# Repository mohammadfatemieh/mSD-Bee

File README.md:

# mSD-Bee
XBee footprint compatible Module with microSD Socket.

* microSD-Socket
* SPI interface
* XBee compatible Pinout (3.3V)
* Open-Source and released under the [Creative Commons Attribution Share-Alike License](https://creativecommons.org/licenses/by-sa/4.0/).
* **[Documentation on learn.watterott.com](https://learn.watterott.com)**

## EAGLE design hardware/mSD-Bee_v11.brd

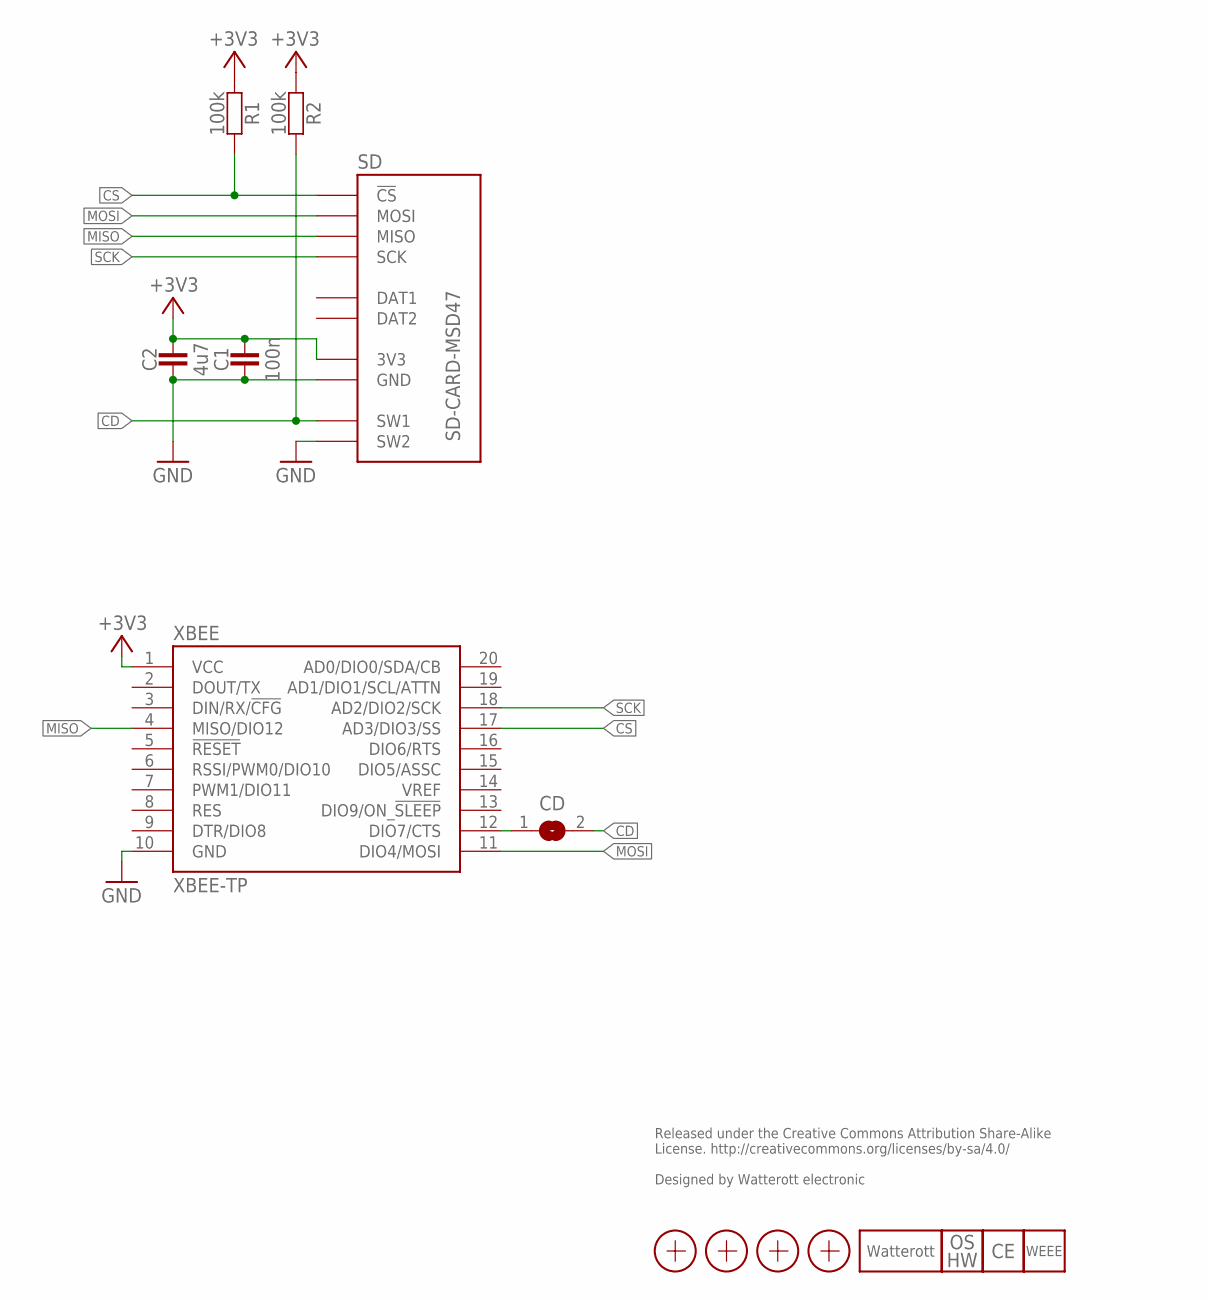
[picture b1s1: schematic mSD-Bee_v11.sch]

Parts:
C1: 100n; C0402
C2: 4u7; C0603
CD: JUMPER2-0603
LOGO3: LOGO_SPARK-2; SPARK_2MM
LOGO4: LOGO_OSHW-2; OSHW_2MM
LOGO5: LOGO_CE-2; CE_2MM
LOGO6: LOGO_WEEE-4; WEEE_4MM
R1, R2: 100k; C0402
SD: SD-CARD-MSD47; SD_47309XXXX
X1, X2, X3, X4: PASSER-07; PASSER_07MM
XBEE: XBEE-TP; XBEE_TP

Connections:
+3V3: C1.2, C2.2, R1.2, R2.2, SD.VCC (3V3), XBEE.1 (VCC)
CD: CD.2, R2.1, SD.SW1
CS: R1.1, SD.CS (!CS), XBEE.17 (AD3/DIO3/SS)
GND: C1.1, C2.1, SD.GND, SD.GND@1 (GND), SD.GND@2 (GND), SD.SW2, XBEE.10 (GND)
INT: CD.1, XBEE.12 (DIO7/CTS)
MISO: SD.MISO, XBEE.4 (MISO/DIO12)
MOSI: SD.MOSI, XBEE.11 (DIO4/MOSI)
SCK: SD.SCK, XBEE.18 (AD2/DIO2/SCK)

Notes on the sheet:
Released under the Creative Commons Attribution Share-Alike License. http://creativecommons.org/licenses/by-sa/4.0/ Designed by Watterott electronic

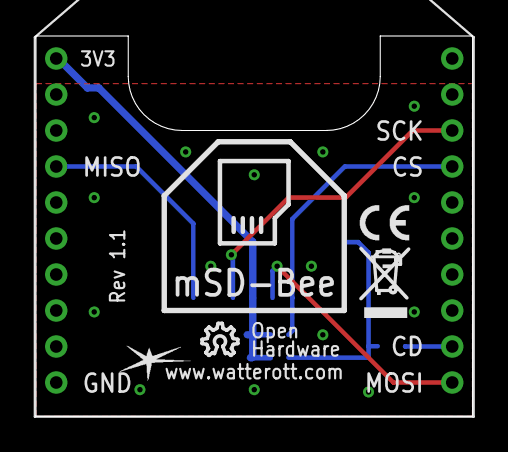
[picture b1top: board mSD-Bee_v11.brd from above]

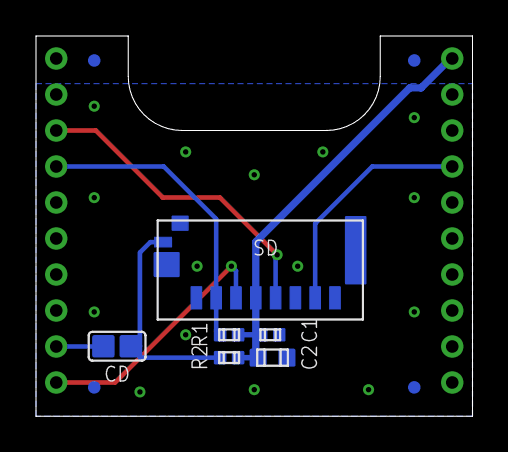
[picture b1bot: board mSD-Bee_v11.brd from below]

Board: 2 copper layers, 24.2 x 21.1 mm, 15 parts (10 on the bottom side), 8 nets.

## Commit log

2018-04-09 added readme
2018-05-03 added layout and schematics
2019-05-14 added picture
